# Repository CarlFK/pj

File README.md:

Pi JTAG hatish.
<https://github.com/CarlFK/pj/wiki>

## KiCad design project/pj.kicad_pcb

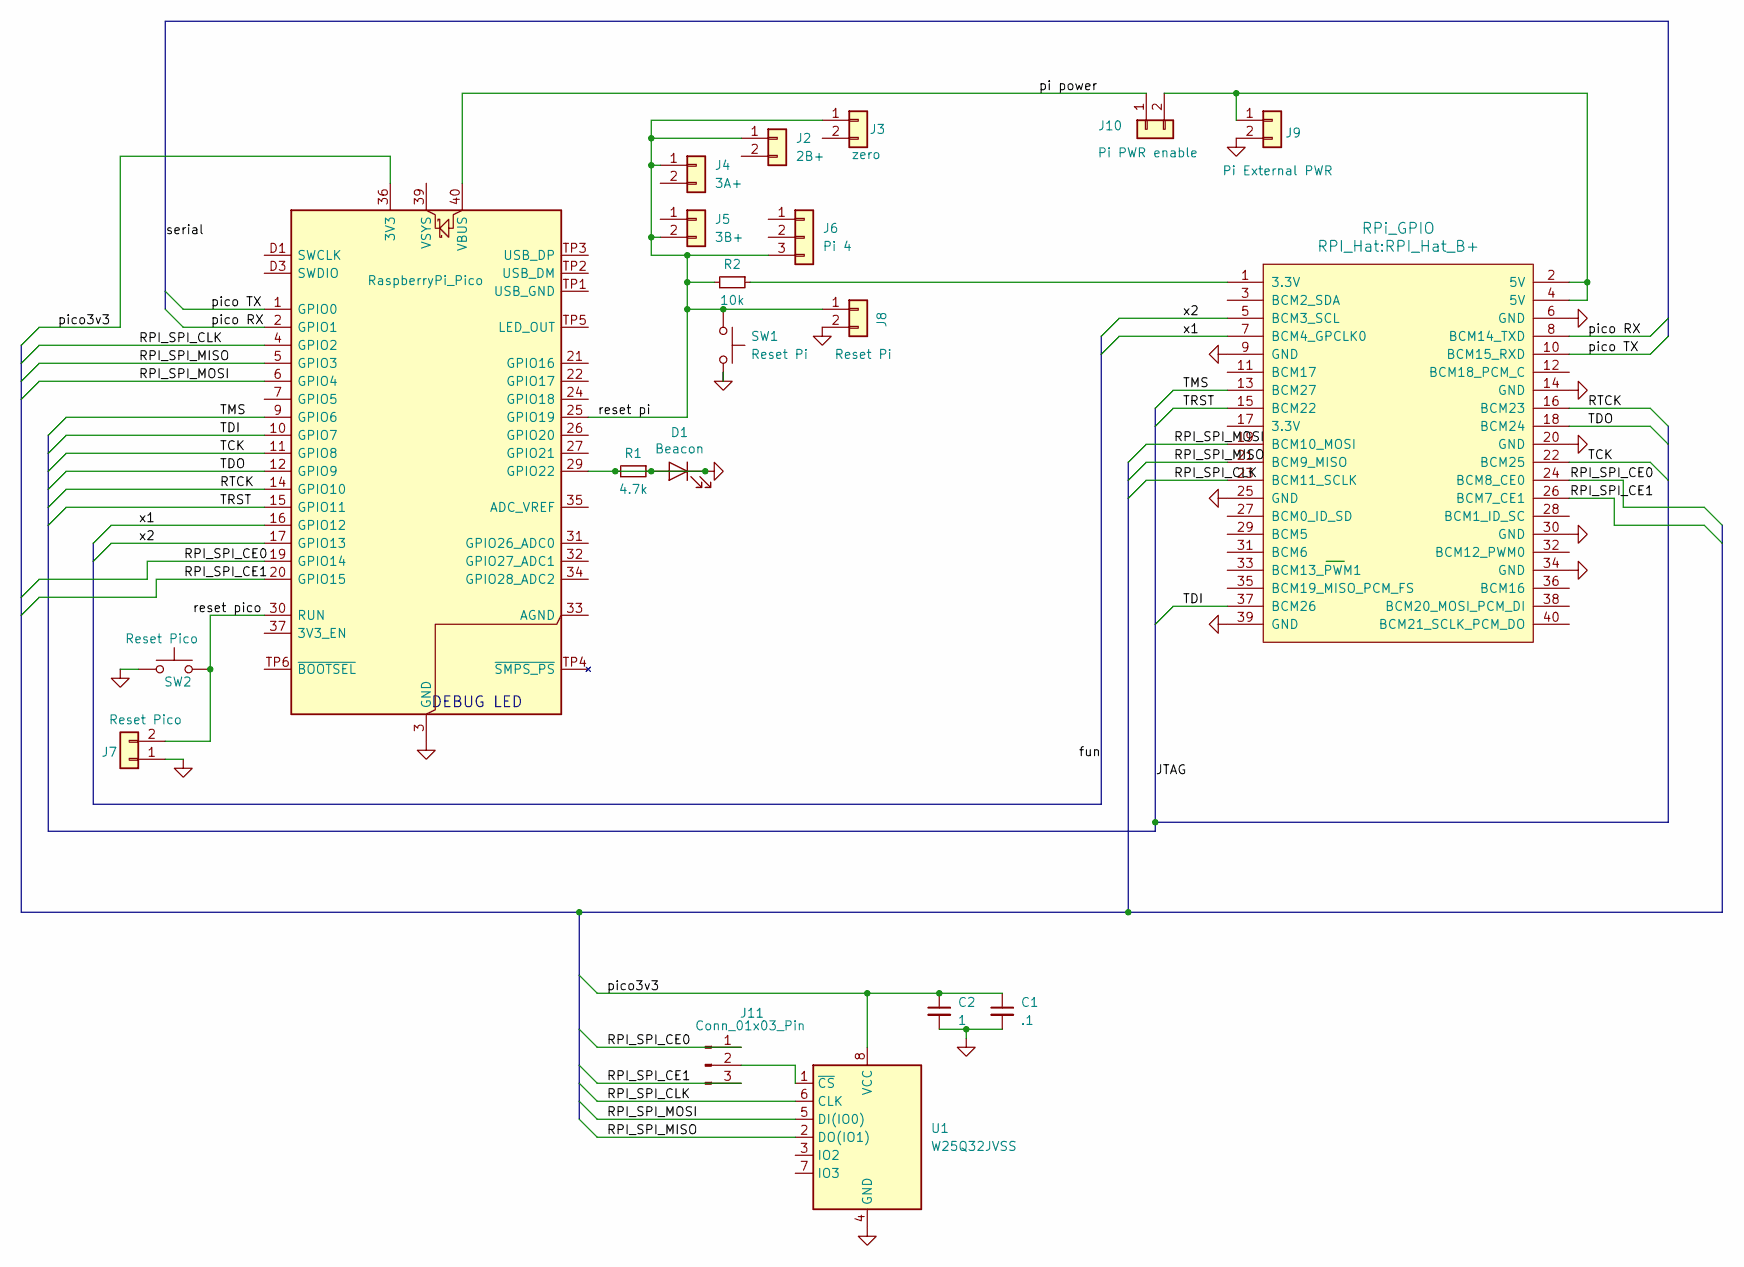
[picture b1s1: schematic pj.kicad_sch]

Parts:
A1: RaspberryPi_Pico; RaspberryPi_Pico_Common
C1: .1; C_0603_1608Metric_Pad1.08x0.95mm_HandSolder
C2: 1; C_0603_1608Metric_Pad1.08x0.95mm_HandSolder
D1: Beacon; LED_0603_1608Metric
J1: RPi_GPIO; RPI_Hat_B+
J2: 2B+; PinSocket_1x02_P2.54mm_Vertical
J3: zero; PinSocket_1x02_P2.54mm_Vertical
J4: 3A+; PinSocket_1x02_P2.54mm_Vertical
J5: 3B+; PinSocket_1x02_P2.54mm_Vertical
J6: Pi 4; PinSocket_1x03_P2.54mm_Vertical
J7: Reset Pico; PinHeader_1x02_P2.54mm_Vertical
J8: Reset Pi; PinHeader_1x02_P2.54mm_Vertical
J9: Pi External PWR; PinHeader_1x02_P2.54mm_Vertical
J10: Pi PWR enable; SolderJumper-2_P1.3mm_Bridged2Bar_Pad1.0x1.5mm
J11: Conn_01x03_Pin; PinHeader_1x03_P2.54mm_Vertical
R1: 4.7k; R_0603_1608Metric
R2: 10k; R_0603_1608Metric
SW1: Reset Pi; SW_PUSH_6mm_H4.3mm
SW2: Reset Pico; SW_PUSH_6mm_H4.3mm
U1: W25Q32JVSS; SOIC-8_5.23x5.23mm_P1.27mm

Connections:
/RPI_SPI_CE0: A1.19 (GPIO14), J1.24 (BCM8_CE0), J11.1
/RPI_SPI_CE1: A1.20 (GPIO15), J1.26 (BCM7_CE1), J11.3
/RPI_SPI_CLK: A1.4 (GPIO2), J1.23 (BCM11_SCLK), U1.6 (CLK)
/RPI_SPI_MISO: A1.5 (GPIO3), J1.21 (BCM9_MISO), U1.2 (DO(IO1))
/RPI_SPI_MOSI: A1.6 (GPIO4), J1.19 (BCM10_MOSI), U1.5 (DI(IO0))
/RTCK: A1.14 (GPIO10), J1.16 (BCM23)
/TCK: A1.11 (GPIO8), J1.22 (BCM25)
/TDI: A1.10 (GPIO7), J1.37 (BCM26)
/TDO: A1.12 (GPIO9), J1.18 (BCM24)
/TMS: A1.9 (GPIO6), J1.13 (BCM27)
/TRST: A1.15 (GPIO11), J1.15 (BCM22)
/pi power: A1.40 (VBUS), J10.1
/pico3v3: A1.36 (3V3), C1.1, C2.1, U1.8 (VCC)
/pico RX: A1.2 (GPIO1), J1.8 (BCM14_TXD)
/pico TX: A1.1 (GPIO0), J1.10 (BCM15_RXD)
/reset pi: A1.25 (GPIO19), J2.1, J3.1, J4.1, J5.2, J6.3, J8.1, R2.2, SW1.1
/x1: A1.16 (GPIO12), J1.7 (BCM4_GPCLK0)
/x2: A1.17 (GPIO13), J1.5 (BCM3_SCL)
GND: A1.3 (GND), A1.8 (GND), A1.13 (GND), A1.18 (GND), A1.23 (GND), A1.28 (GND), A1.29 (GPIO22), A1.38 (GND), A1.D2 (GND), C1.2, C2.2, D1.1 (K), D1.2 (A), J1.6 (GND), J1.9 (GND), J1.14 (GND), J1.20 (GND), J1.25 (GND), J1.30 (GND), J1.34 (GND), J1.39 (GND), J7.1, J8.2, J9.2, R1.1, R1.2, SW1.2, SW2.1, U1.4 (GND)
unnamed: A1.30 (RUN), J7.2, SW2.2
unnamed: J1.1 (3.3V), R2.1
unnamed: J1.2 (5V), J1.4 (5V), J9.1, J10.2
unnamed: J11.2, U1.1 (~CS)

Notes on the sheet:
DEBUG LED

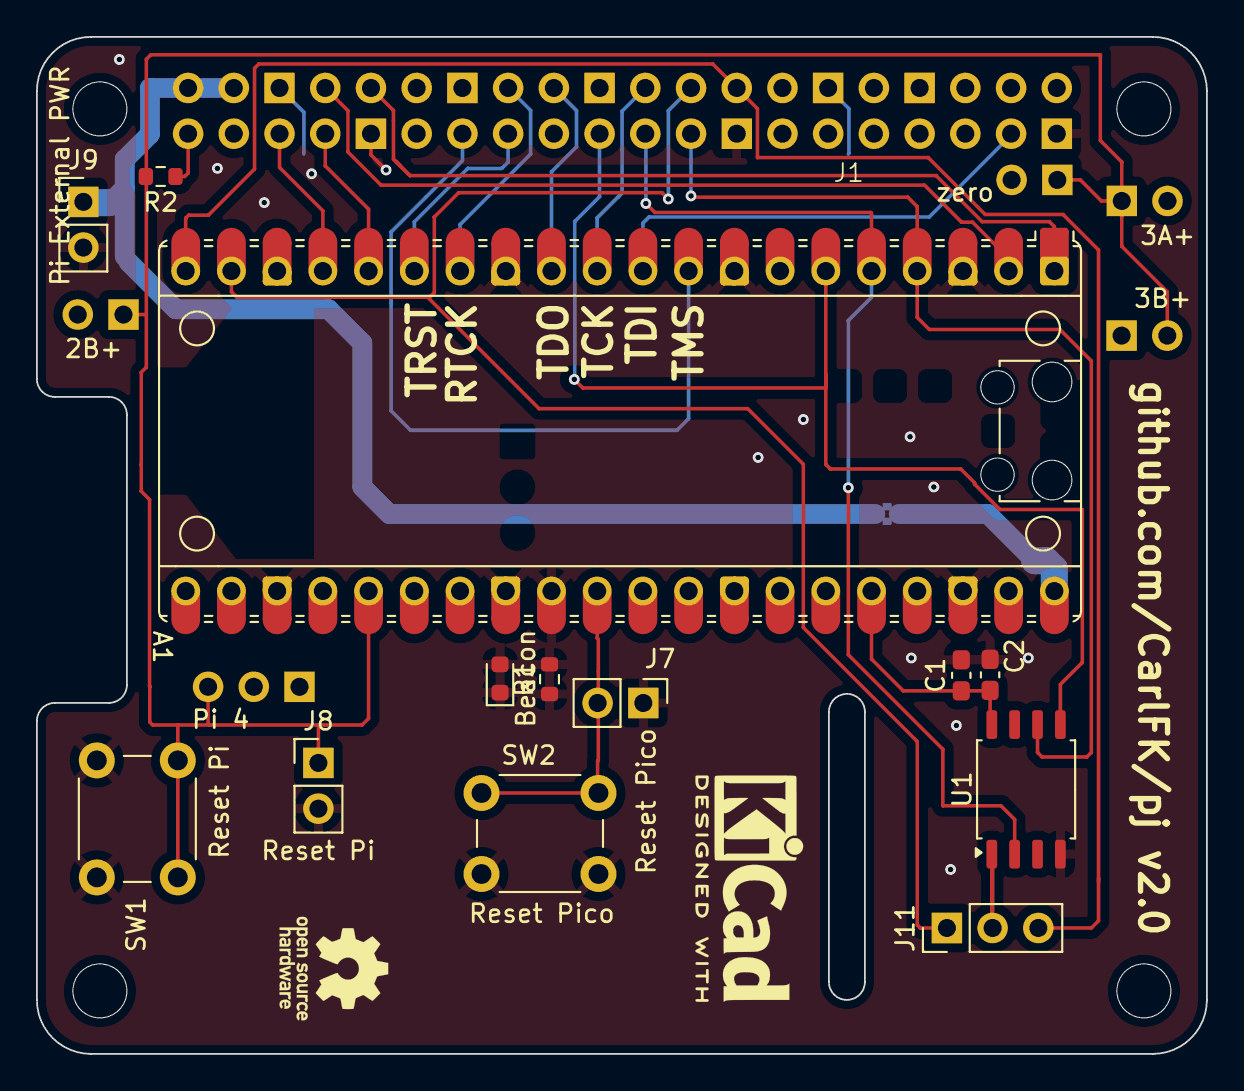
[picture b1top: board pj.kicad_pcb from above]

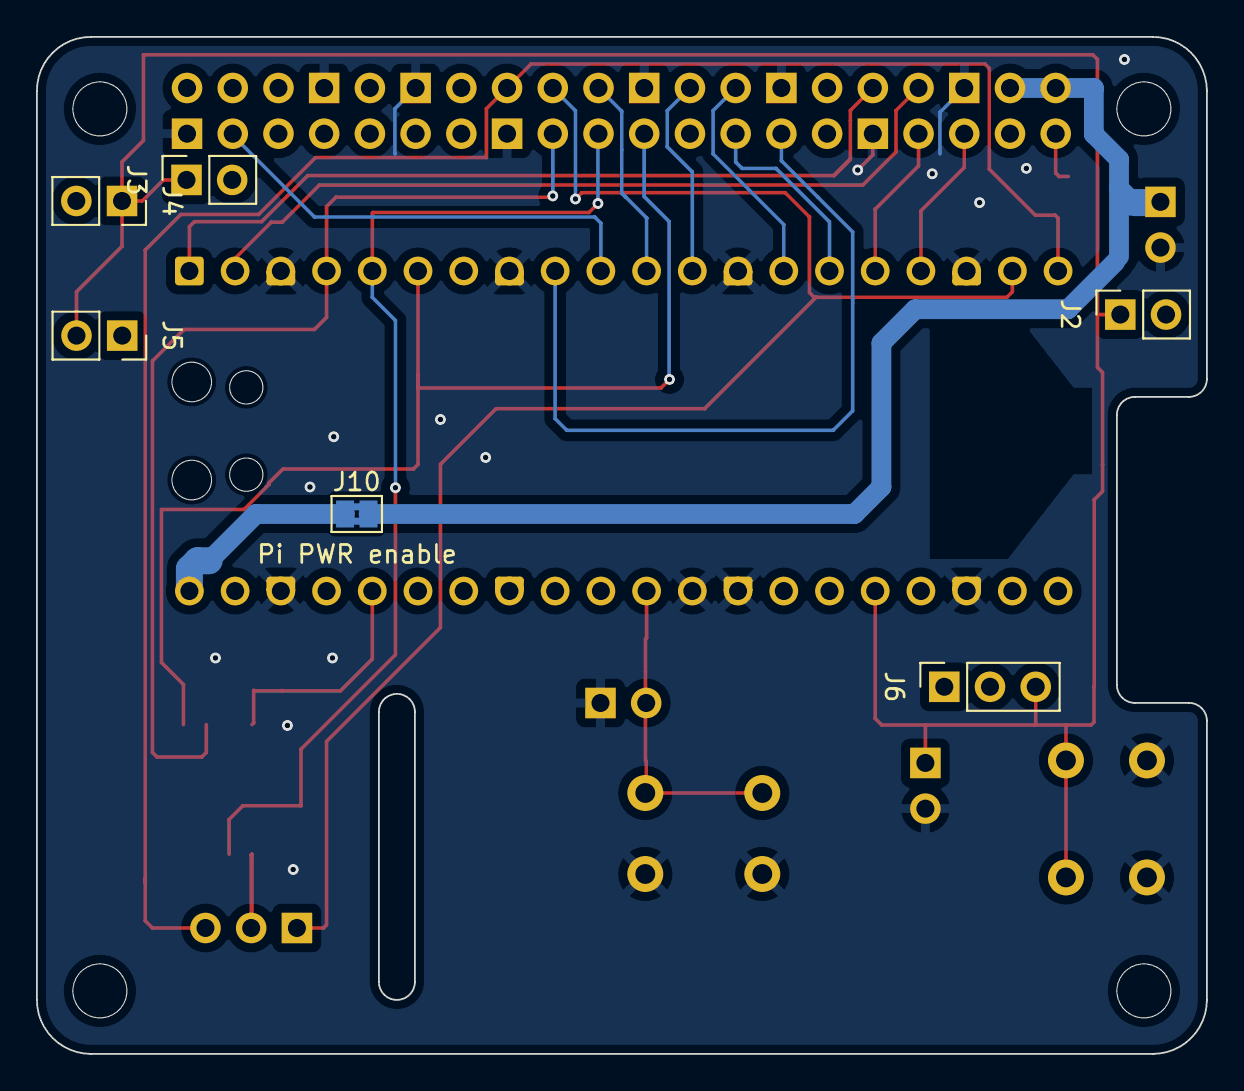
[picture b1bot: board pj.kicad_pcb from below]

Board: 2 copper layers, 65.0 x 56.5 mm, 20 parts (6 on the bottom side), 23 nets.

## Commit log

2024-10-22 jtag, uart, power.
2024-10-22 add ki-lime-pi-pico submodule
2024-10-23 Add all the RUNs
2024-10-23 remove pi dxf files
2024-10-23 burn down the pdb. try again.
2024-10-23 connected vcc, tx/rx and added the headers to the pcb.
2024-10-24 all symbols linked to PCB
2024-10-24 now with reset buttons
2024-10-24 now with grounds
2024-10-24 RUN button GND
2024-10-24 fix cruft on J8 pin 2
2024-10-24 ground plane on both sides
2024-10-24 Add Pico PWR and External PoWR
2024-10-25 pwr eneble
2024-10-25 re-route power for more power
2024-10-25 tweek the RUN holes
2024-10-25 add JTAG pin labels
2024-10-25 beacon
2024-10-25 oshw logo
2024-10-25 add gpio bus, lables and KiCad logo
2024-10-26 added 40 pin socket
2024-10-26 group jtag io
2024-10-26 move the pi reset jumper/button schematic
2024-10-26 hook some gpios for kicks
2024-10-26 move holes to make room for more holes
2024-10-26 move reset over one, move reset headert to make room for row of holes.
2024-10-26 add 16 holes to put things in later.
2024-10-26 ground plane, reroute some reset
2024-10-26 add missing connection to hole.
2024-10-26 no DRC errors
2024-10-26 2.54 for all the headers.
2024-10-26 set f.silk, again.
2024-10-26 set a few more f.silk, again.
2024-10-27 busses everywere. with better labels.
2024-10-27 py to dump netlists
2024-10-27 lable the serial bus
2024-10-28 document source of kicad_parser
2024-10-28 usage docs
2024-10-28 add command line parameters.
2024-10-28 more usage docs.
2024-10-29 label buses jtag and fun
2024-10-29 change serial bus label to global.
2024-10-29 change global labels to local.
2024-11-01 image for README.md
2024-11-04 pi setup
2024-11-09 scripts to setup sd cards
2024-11-10 config.txt
2024-11-15 start adding SPI flash
2024-11-30 spi sch
2024-12-11 add spi symbol
2024-12-11 removing debug header
2024-12-12 added spi, moved zero run
2024-12-12 done with spi
2024-12-12 v2.0
2024-12-12 move OH logo, remove some extra vias
2024-12-20 more cli args
2024-12-20 add license file.
